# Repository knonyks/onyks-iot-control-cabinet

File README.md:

# Onyks IoT Control Cabinet

## Description

This device is part of the IoT project, which this part functions as locker for the cabins.
The devices is equiped with RFID MIFARE detector which detects student ID cards, it also has Wi-fi and Bletooth connection for database access.

## Features
* Two ways of power supply:
    - Terminal block;
    - DC Jack;
* Access for JTAG I/O ports;
* Access for programmer I/O ports;
* GPIO ports with GND;
* A buzzer turns on when the cabinet opens;
* An external header for an NFC external sensor by SPI transmission;
* An LED diod;
* Boot and Reset buttons;
* An external input for open the lock by e.g an external button;
* A button for opening the lock;
* Two ways of connecting the lock
    - a pin header;
    - terminal block;
* The voltage which is on the lock I/O port is like the power supply input voltage, e.g. when we have 12 V supply we have 12 V on the lock I/O ports;
* M6 screw holes to mounting.

Teorically when we have:
* 12 V, 2A (24 W) power supply we can power the lock which need 12 V and 1.2 A;
* 9 V, 2 A (18 W) power supply we can power the lock which need 9 V and 1 A;
* If the buzzer was replaced with higher voltage buzzer, then the device can operate with 24 V, 1 A (24 W) power supply;

* Used buzzer voltage range : 6 V - 18 V.

### Schematic

[[LINK]](docs/schematics.pdf)

## Images

#### Connection schematic with an external NFC module

### PCB

#### PCB View

#### 3D View

## Authors
* Karol Ambroziński
* Jakub Jastrzębski

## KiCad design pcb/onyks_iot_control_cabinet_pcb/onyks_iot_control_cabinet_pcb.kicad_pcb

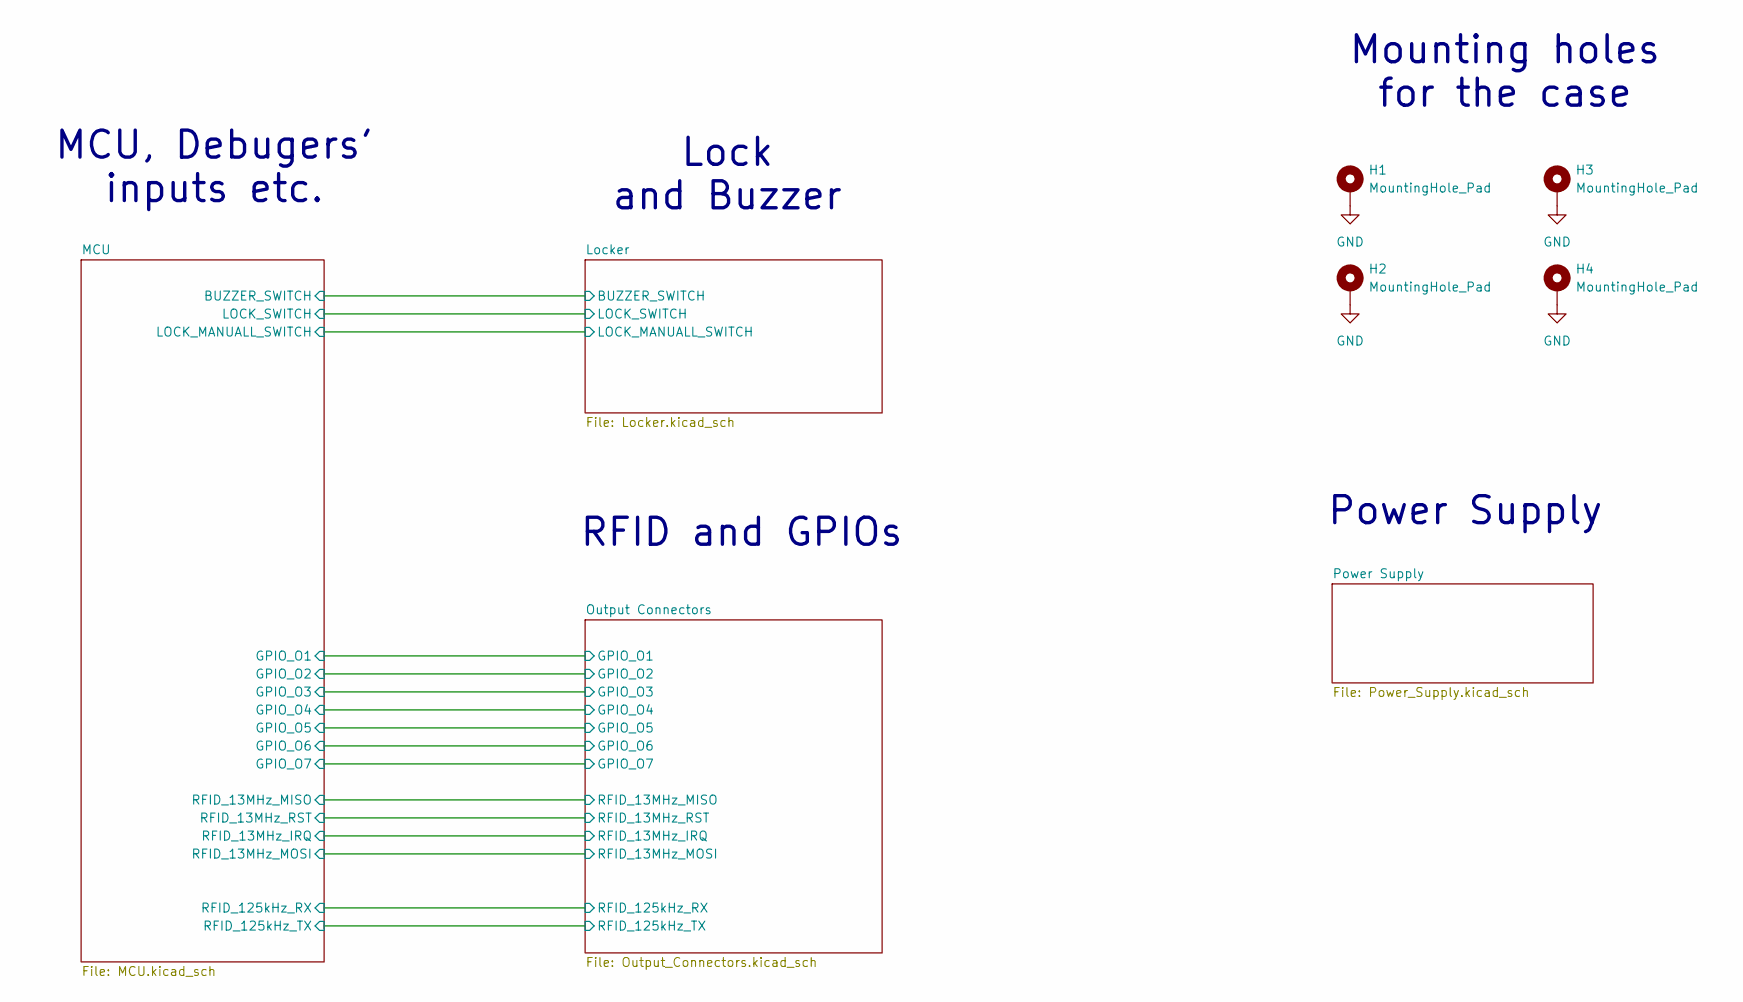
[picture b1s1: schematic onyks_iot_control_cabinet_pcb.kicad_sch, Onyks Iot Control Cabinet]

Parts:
H1, H2, H3, H4: MountingHole_Pad; MountingHole_3.2mm_M3_DIN965_Pad_TopBottom

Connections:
GND: H1.1, H2.1, H3.1, H4.1; also elsewhere on the board

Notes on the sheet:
Power Supply
RFID and GPIOs
Mounting holes for the case
MCU, Debugers' inputs etc.
Lock and Buzzer

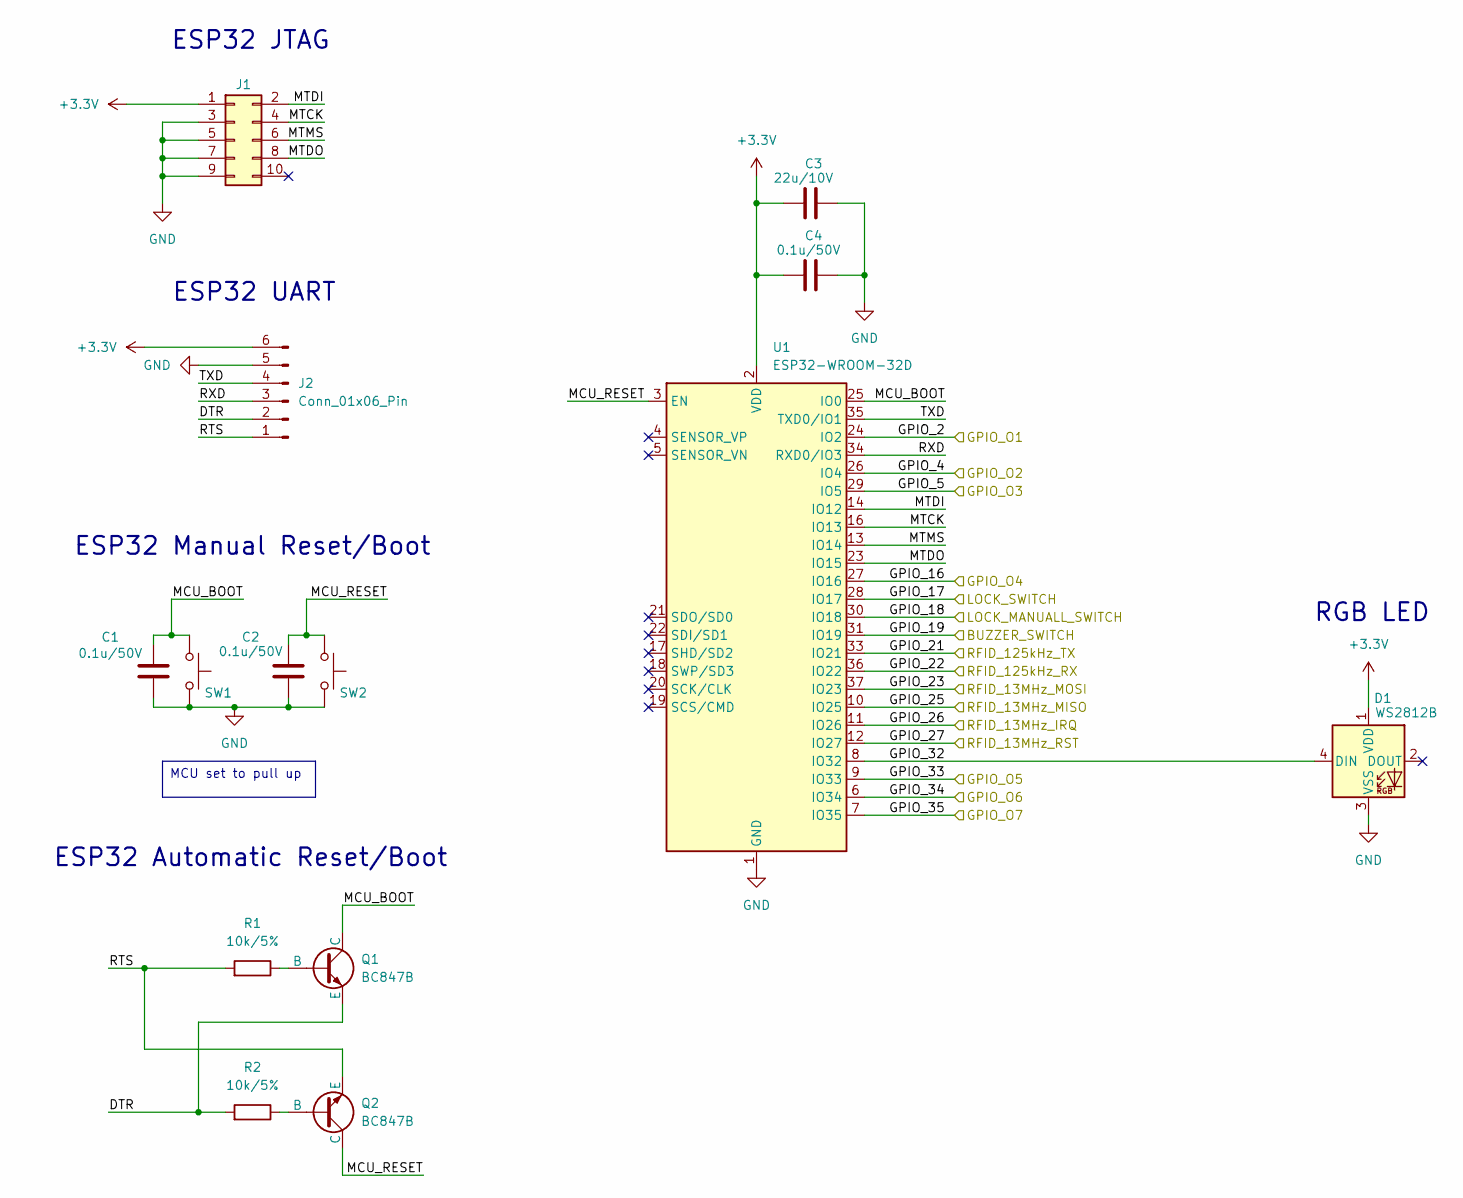
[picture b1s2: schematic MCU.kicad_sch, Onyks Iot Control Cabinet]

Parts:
C1, C2, C4: 0.1u/50V; C_0603_1608Metric
C3: 22u/10V; C_0603_1608Metric
D1: WS2812B; LED_WS2812B_PLCC4_5.0x5.0mm_P3.2mm
J1: Conn_02x05_Odd_Even; PinHeader_2x05_P2.54mm_Vertical
J2: Conn_01x06_Pin; PinHeader_1x06_P2.54mm_Vertical
Q1, Q2: BC847B; SOT-23-3
R1, R2: 10k/5%; R_0805_2012Metric_Pad1.20x1.40mm_HandSolder
SW1, SW2: SW_Push; SW_Tactile_SPST_NO_Straight_CK_PTS636Sx25SMTRLFS
U1: ESP32-WROOM-32D

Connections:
+3.3V: C3.1, C4.1, D1.1 (VDD), J1.1, J2.6, U1.2 (VDD); also elsewhere on the board
/MCU/DTR: J2.2, Q1.3 (E), R2.2
/MCU/GPIO_2: U1.24 (IO2); also elsewhere on the board
/MCU/GPIO_4: U1.26 (IO4); also elsewhere on the board
/MCU/GPIO_5: U1.29 (IO5); also elsewhere on the board
/MCU/GPIO_16: U1.27 (IO16); also elsewhere on the board
/MCU/GPIO_17: U1.28 (IO17); also elsewhere on the board
/MCU/GPIO_18: U1.30 (IO18); also elsewhere on the board
/MCU/GPIO_19: U1.31 (IO19); also elsewhere on the board
/MCU/GPIO_21: U1.33 (IO21); also elsewhere on the board
/MCU/GPIO_22: U1.36 (IO22); also elsewhere on the board
/MCU/GPIO_23: U1.37 (IO23); also elsewhere on the board
/MCU/GPIO_25: U1.10 (IO25); also elsewhere on the board
/MCU/GPIO_26: U1.11 (IO26); also elsewhere on the board
/MCU/GPIO_27: U1.12 (IO27); also elsewhere on the board
/MCU/GPIO_32: D1.4 (DIN), U1.8 (IO32)
/MCU/GPIO_33: U1.9 (IO33); also elsewhere on the board
/MCU/GPIO_34: U1.6 (IO34); also elsewhere on the board
/MCU/GPIO_35: U1.7 (IO35); also elsewhere on the board
/MCU/MCU_BOOT: C1.1, Q1.1 (C), SW1.1, U1.25 (IO0)
/MCU/MCU_RESET: C2.1, Q2.1 (C), SW2.1, U1.3 (EN)
/MCU/MTCK: J1.4, U1.16 (IO13)
/MCU/MTDI: J1.2, U1.14 (IO12)
/MCU/MTDO: J1.8, U1.23 (IO15)
/MCU/MTMS: J1.6, U1.13 (IO14)
/MCU/RTS: J2.1, Q2.3 (E), R1.2
/MCU/RXD: J2.3, U1.34 (RXD0/IO3)
/MCU/TXD: J2.4, U1.35 (TXD0/IO1)
GND: C1.2, C2.2, C3.2, C4.2, D1.3 (VSS), J1.3, J1.5, J1.7, J1.9, J2.5, SW1.2, SW2.2, U1.1 (GND), U1.15 (GND), U1.38 (GND), U1.39 (GND); also elsewhere on the board
unnamed: Q1.2 (B), R1.1
unnamed: Q2.2 (B), R2.1

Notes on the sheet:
ESP32 UART
RGB LED
ESP32 Automatic Reset/Boot
ESP32 Manual Reset/Boot
ESP32 JTAG
MCU set to pull up

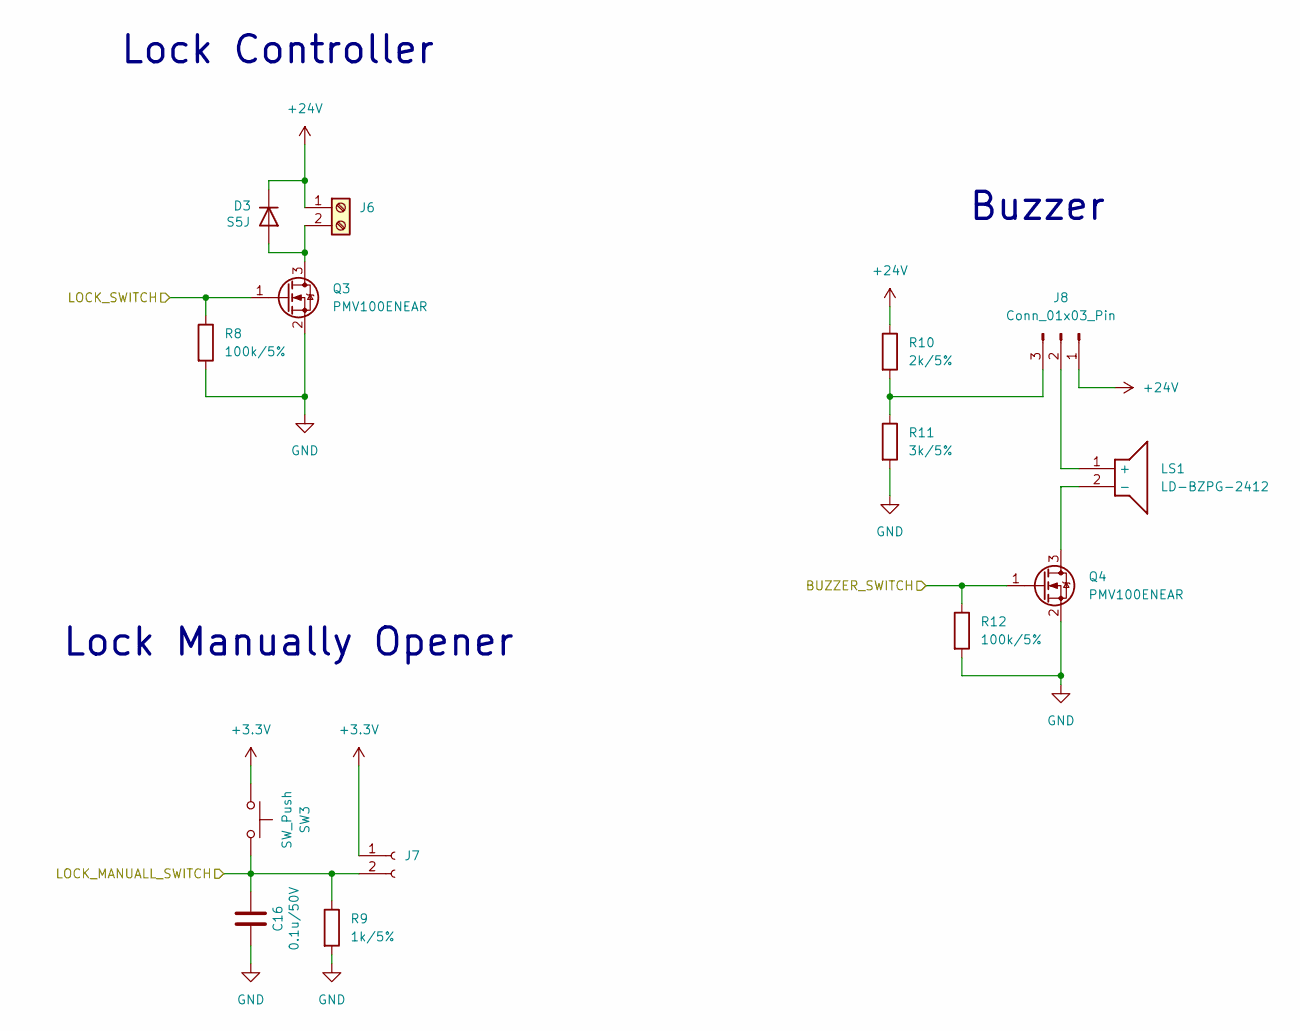
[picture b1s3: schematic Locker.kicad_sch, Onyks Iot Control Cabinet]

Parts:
C16: 0.1u/50V; C_0603_1608Metric
D3: S5J; D_SMC
J6: Screw_Terminal_01x02; TerminalBlock_Altech_AK300-2_P5.00mm
J7: Conn_01x02_Socket; PinHeader_1x02_P2.54mm_Vertical
J8: Conn_01x03_Pin; PinHeader_1x03_P2.54mm_Vertical
LS1: LD-BZPG-2412; LDBZPG2412; Manufacturer_Part_Number LD-BZPG-2412
Q3, Q4: PMV100ENEAR; SOT-23
R8, R12: 100k/5%; R_0805_2012Metric_Pad1.20x1.40mm_HandSolder
R9: 1k/5%; R_0805_2012Metric_Pad1.20x1.40mm_HandSolder
R10: 2k/5%; R_0805_2012Metric_Pad1.20x1.40mm_HandSolder
R11: 3k/5%; R_0805_2012Metric_Pad1.20x1.40mm_HandSolder
SW3: SW_Push; SW_Tactile_SPST_NO_Straight_CK_PTS636Sx25SMTRLFS

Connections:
+3.3V: J7.1, SW3.1; also elsewhere on the board
+24V: D3.1 (K), J6.1, J8.1, R10.1; also elsewhere on the board
/MCU/GPIO_17: Q3.1 (G), R8.1; also elsewhere on the board
/MCU/GPIO_18: C16.1, J7.2, R9.1, SW3.2; also elsewhere on the board
/MCU/GPIO_19: Q4.1 (G), R12.1; also elsewhere on the board
GND: C16.2, Q3.2 (S), Q4.2 (S), R8.2, R9.2, R11.2, R12.2; also elsewhere on the board
unnamed: D3.2 (A), J6.2, Q3.3 (D)
unnamed: J8.2, LS1.1 (+)
unnamed: J8.3, R10.2, R11.1
unnamed: LS1.2 (-), Q4.3 (D)

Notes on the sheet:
Lock Manually Opener
Lock Controller
Buzzer

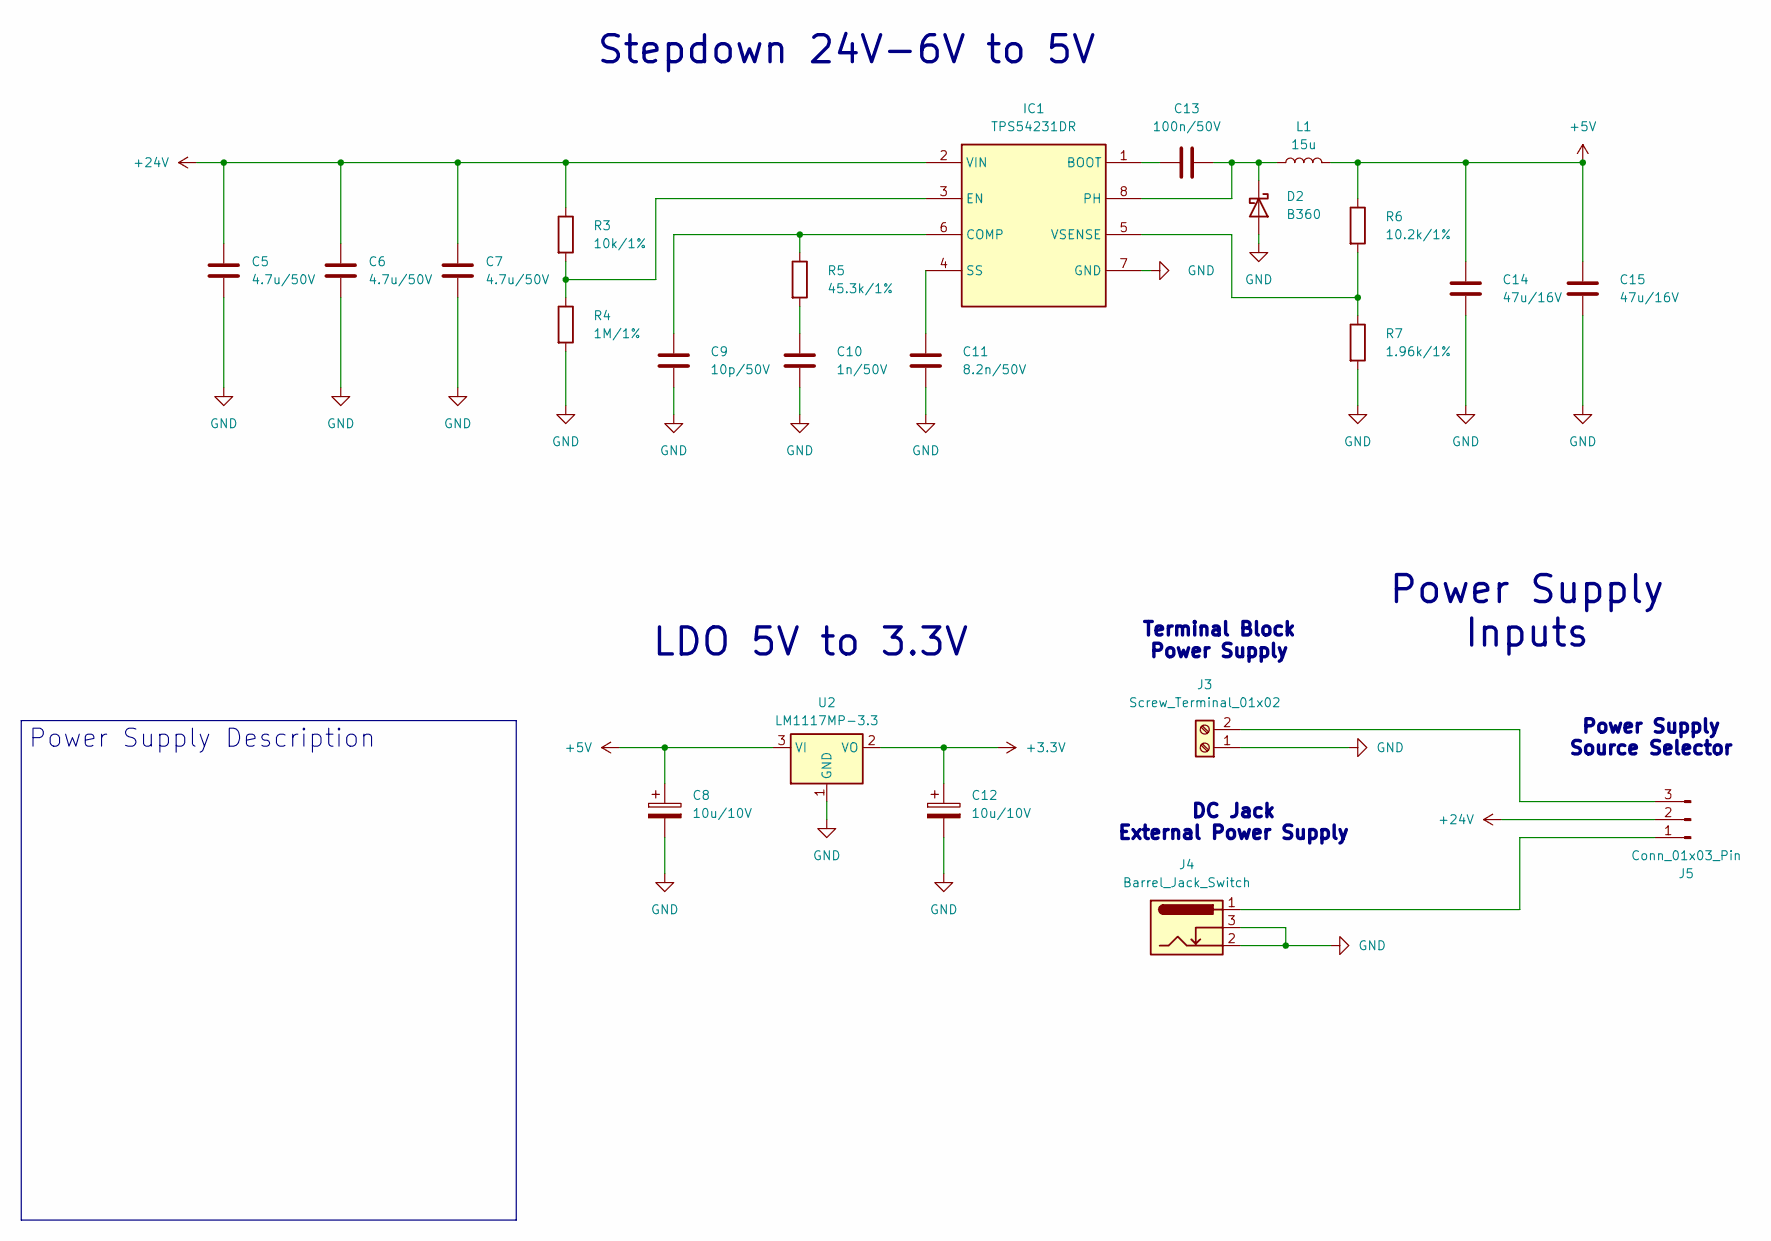
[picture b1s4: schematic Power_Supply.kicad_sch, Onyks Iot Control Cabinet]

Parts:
C5, C6, C7: 4.7u/50V; C_0603_1608Metric
C8, C12: 10u/10V; C_0603_1608Metric
C9: 10p/50V; C_0603_1608Metric
C10: 1n/50V; C_0603_1608Metric
C11: 8.2n/50V; C_0603_1608Metric
C13: 100n/50V; C_0603_1608Metric
C14, C15: 47u/16V; C_0603_1608Metric
D2: B360; D_SMC
IC1: TPS54231DR; SOIC127P600X175-8N; Manufacturer_Part_Number TPS54231DR
J3: Screw_Terminal_01x02; TerminalBlock_Altech_AK300-2_P5.00mm
J4: Barrel_Jack_Switch; BarrelJack_CLIFF_FC681465S_SMT_Horizontal
J5: Conn_01x03_Pin; PinHeader_1x03_P2.54mm_Vertical
L1: 15u; L_12x12mm_H4.5mm
R3: 10k/1%; R_0805_2012Metric_Pad1.20x1.40mm_HandSolder
R4: 1M/1%; R_0805_2012Metric_Pad1.20x1.40mm_HandSolder
R5: 45.3k/1%; R_0805_2012Metric_Pad1.20x1.40mm_HandSolder
R6: 10.2k/1%; R_0805_2012Metric_Pad1.20x1.40mm_HandSolder
R7: 1.96k/1%; R_0805_2012Metric_Pad1.20x1.40mm_HandSolder
U2: LM1117MP-3.3; SOT-223-3_TabPin2

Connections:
+3.3V: C12.1, U2.2 (VO); also elsewhere on the board
+5V: C8.1, C14.1, C15.1, L1.2, R6.1, U2.3 (VI); also elsewhere on the board
+24V: C5.1, C6.1, C7.1, IC1.2 (VIN), J5.2, R3.1; also elsewhere on the board
GND: C5.2, C6.2, C7.2, C8.2, C9.2, C10.2, C11.2, C12.2, C14.2, C15.2, D2.2 (A), IC1.7 (GND), J3.1, J4.2, J4.3, R4.2, R7.2, U2.1 (GND); also elsewhere on the board
unnamed: C10.1, R5.2
unnamed: C13.2, D2.1 (K), IC1.8 (PH), L1.1
unnamed: C13.1, IC1.1 (BOOT)
unnamed: C9.1, IC1.6 (COMP), R5.1
unnamed: IC1.3 (EN), R3.2, R4.1
unnamed: C11.1, IC1.4 (SS)
unnamed: IC1.5 (VSENSE), R6.2, R7.1
unnamed: J3.2, J5.3
unnamed: J4.1, J5.1

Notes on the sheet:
DC Jack External Power Supply
LDO 5V to 3.3V
Stepdown 24V-6V to 5V
Power Supply Source Selector
Terminal Block Power Supply
Power Supply Inputs
Power Supply Description

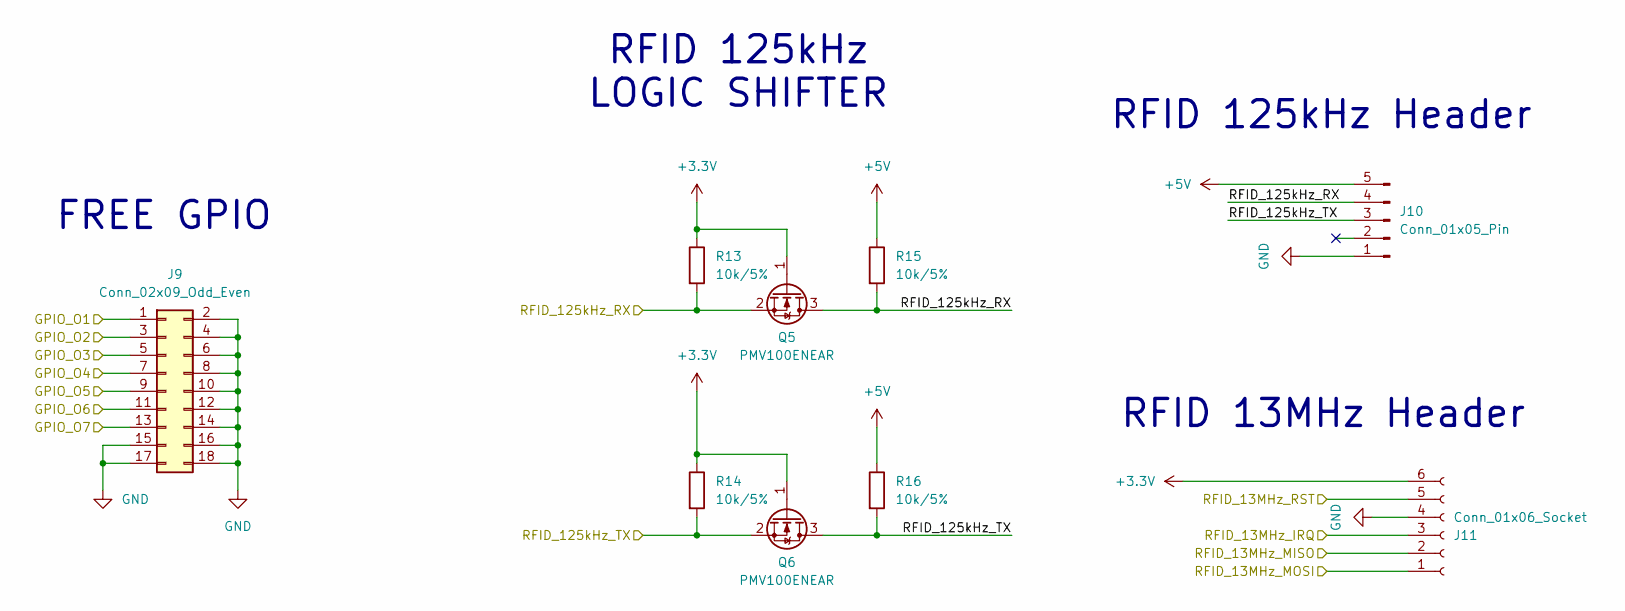
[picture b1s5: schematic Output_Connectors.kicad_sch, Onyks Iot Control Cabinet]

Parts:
J9: Conn_02x09_Odd_Even; PinHeader_2x09_P2.54mm_Vertical
J10: Conn_01x05_Pin; PinHeader_1x05_P2.54mm_Vertical
J11: Conn_01x06_Socket; PinHeader_1x06_P2.54mm_Vertical
Q5, Q6: PMV100ENEAR; SOT-23
R13, R14, R15, R16: 10k/5%; R_0805_2012Metric_Pad1.20x1.40mm_HandSolder

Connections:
+3.3V: J11.6, Q5.1 (G), Q6.1 (G), R13.1, R14.1; also elsewhere on the board
+5V: J10.5, R15.1, R16.1; also elsewhere on the board
/MCU/GPIO_2: J9.1; also elsewhere on the board
/MCU/GPIO_4: J9.3; also elsewhere on the board
/MCU/GPIO_5: J9.5; also elsewhere on the board
/MCU/GPIO_16: J9.7; also elsewhere on the board
/MCU/GPIO_21: J10.3, Q6.2 (S), Q6.3 (D), R14.2, R16.2; also elsewhere on the board
/MCU/GPIO_22: J10.4, Q5.2 (S), Q5.3 (D), R13.2, R15.2; also elsewhere on the board
/MCU/GPIO_23: J11.1; also elsewhere on the board
/MCU/GPIO_25: J11.2; also elsewhere on the board
/MCU/GPIO_26: J11.3; also elsewhere on the board
/MCU/GPIO_27: J11.5; also elsewhere on the board
/MCU/GPIO_33: J9.9; also elsewhere on the board
/MCU/GPIO_34: J9.11; also elsewhere on the board
/MCU/GPIO_35: J9.13; also elsewhere on the board
GND: J9.2, J9.4, J9.6, J9.8, J9.10, J9.12, J9.14, J9.15, J9.16, J9.17, J9.18, J10.1, J11.4; also elsewhere on the board

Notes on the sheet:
RFID 125kHz LOGIC SHIFTER
RFID 13MHz Header
RFID 125kHz Header
FREE GPIO

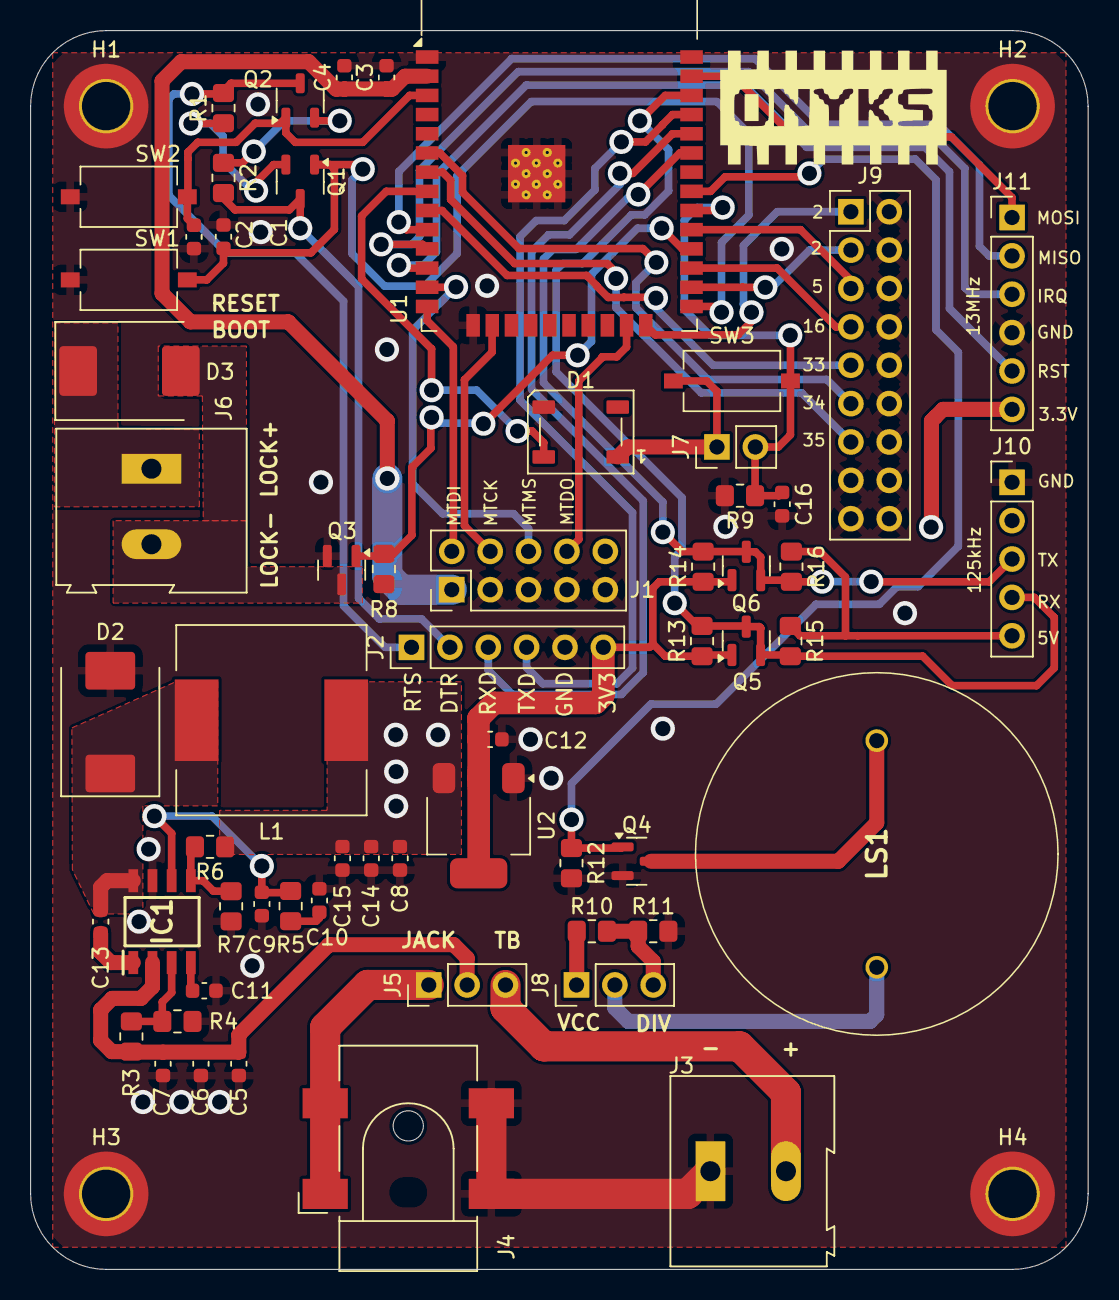
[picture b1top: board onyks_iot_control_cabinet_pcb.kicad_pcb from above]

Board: 2 copper layers, 70.0 x 82.0 mm, 64 parts (0 on the bottom side), 46 nets.

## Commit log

2024-11-09 Pierwsze szkice schematu
2024-11-10 Poczatki NFC
2024-11-10 NFC - znaleziono dokumentację projektową xD
2024-11-16 Booting/Reset circuit change
2024-11-16 Small changes to the buttons and lock control
2024-11-17 Add the nfc connector with external outputs
2024-11-19 Updates of the schematics and add the README.md; add a step-down for 3V3
2024-11-19 Fix the folders and files names - Vol. 1
2024-11-19 Add a buzzer controller to the schematic
2024-11-21 Added Connectors, Fixed buttons
2024-11-21 Add one note
2024-12-01 Fix the project; cleaning up the things
2024-12-01 Assignment some footprints to symbols
2024-12-01 PCB - Finished, needs additional confirmation
2024-12-02 Edit .gitignore
2024-12-05 Change some elements footprints
2024-12-08 PCB's update
2024-12-08 Minor corrections/Rules
2024-12-08 Change the connector of GPIOs
2024-12-08 Patching GND for Free GPIO Connections
2024-12-09 Edit of README.md
2024-12-10 Fixed minor mistakes (name of MOS component)
2024-12-10 README Update
2025-02-02 Add new rules, change JTAG and VCC polygon plane
2025-02-03 Changed VCC polygon into GND polygon, VCC traces added
2025-02-06 Fixing footprint
2025-02-06 Add pins for the jumper and choosing the power supply; also add connection for JTAG 3V3
2025-02-14 Adding Thermal Relieves, Via stiching, Components Silkscreen
2025-02-17 Onyks - Karol narzekal <3
2025-02-17 Almost final fixes of the PCB?
2025-02-17 Cleaning up the repo
2025-03-05 Adding 3D models
2025-03-06 Karol can't add mounting holes/Added
2025-03-14 PCB Update for package
2025-03-18 Redrawing schematics
2025-03-27 New fixes of schematics
2025-03-27 Quick Fixes
2025-04-03 Final fixes? - update the power supply
2025-04-03 Schematic last check
2025-06-20 PCB Overhaul
2025-06-23 Round corners and the logo
2025-06-24 Add descriptions to ports
2025-06-24 Silkscreen changes
2025-07-14 PCB Review 2.0 Update
2025-07-15 Update the PCB and schematics; add the potentiometer
2025-07-23 Update of the power supply; change of the stepdown from 3.3V to 5V on the output without updating the PCB
2025-08-26 Update of the power supply and added the header for 125kHz RFID
2025-08-26 Logic Shifter for RFID 125 KHz
2025-10-02 Schematics update; power supply and footprints fixes
2025-10-02 PCB Ressurection
2025-10-02 PCB Update
2025-10-04 Updated PCB 2
2025-10-06 PCB 3.3V fix
2025-10-06 PCB Update 3
2025-10-06 PCB descriptions
2025-10-26 Gerber files update
